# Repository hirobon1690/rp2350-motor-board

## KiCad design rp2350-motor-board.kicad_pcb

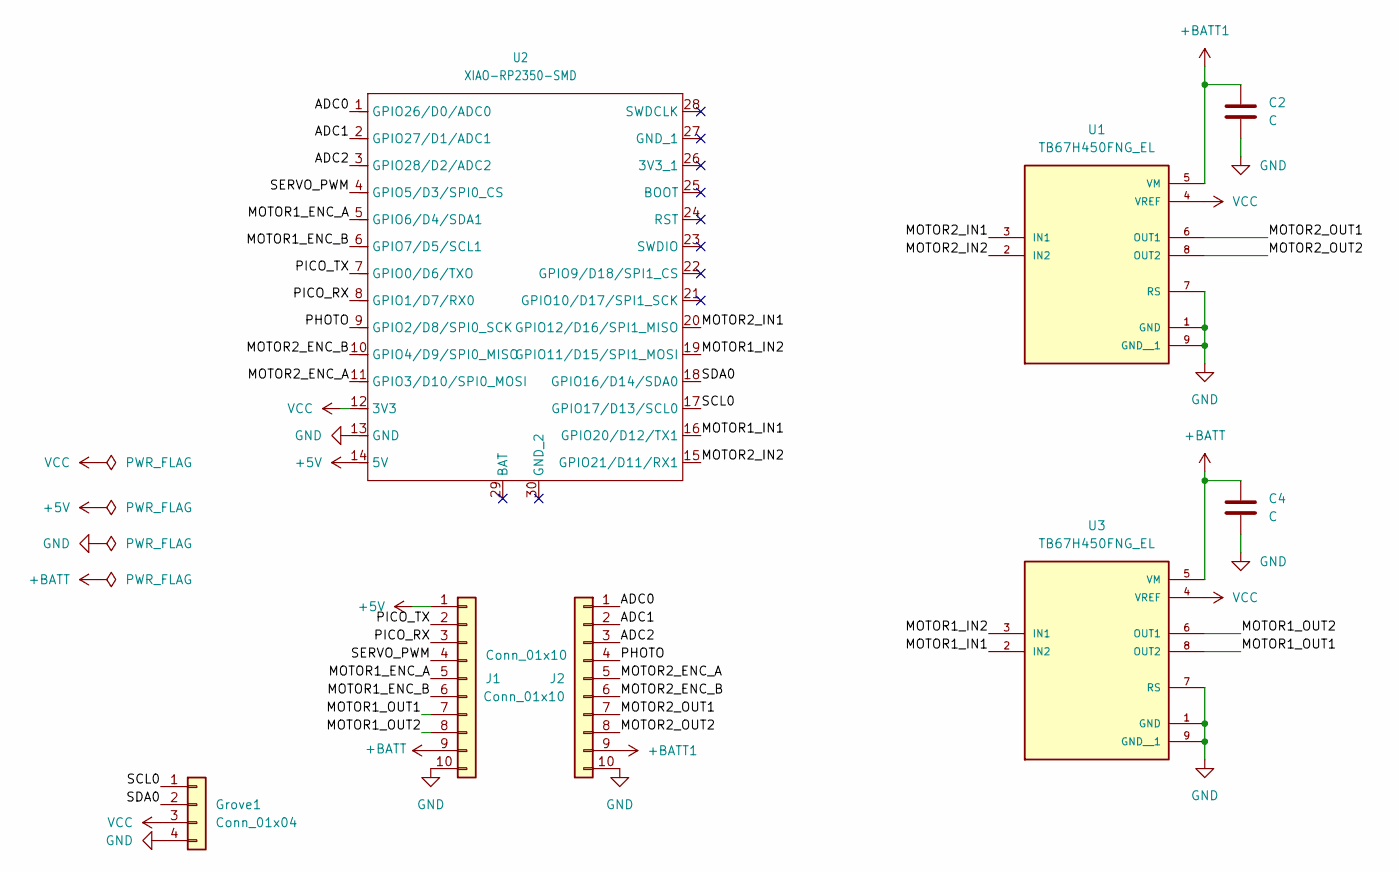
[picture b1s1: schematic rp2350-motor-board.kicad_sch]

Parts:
C2, C4: C; C_0805_2012Metric_Pad1.18x1.45mm_HandSolder
Grove1: Conn_01x04; JST_PH_S4B-PH-K_1x04_P2.00mm_Horizontal
J1, J2: Conn_01x10; PinSocket_1x10_P2.54mm_Vertical
U1, U3: TB67H450FNG_EL; SOIC127P599X175-9N; PARTREV 3.0
U2: XIAO-RP2350-SMD

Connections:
+5V: J1.1, U2.14 (5V)
+BATT: C4.1, J1.9, U3.5 (VM)
+BATT1: C2.1, J2.9, U1.5 (VM)
/ADC0: J2.1, U2.1 (GPIO26/D0/ADC0)
/ADC1: J2.2, U2.2 (GPIO27/D1/ADC1)
/ADC2: J2.3, U2.3 (GPIO28/D2/ADC2)
/MOTOR1_ENC_A: J1.5, U2.5 (GPIO6/D4/SDA1)
/MOTOR1_ENC_B: J1.6, U2.6 (GPIO7/D5/SCL1)
/MOTOR1_IN1: U2.16 (GPIO20/D12/TX1), U3.2 (IN2)
/MOTOR1_IN2: U2.19 (GPIO11/D15/SPI1_MOSI), U3.3 (IN1)
/MOTOR1_OUT1: J1.7, U3.8 (OUT2)
/MOTOR1_OUT2: J1.8, U3.6 (OUT1)
/MOTOR2_ENC_A: J2.5, U2.11 (GPIO3/D10/SPI0_MOSI)
/MOTOR2_ENC_B: J2.6, U2.10 (GPIO4/D9/SPI0_MISO)
/MOTOR2_IN1: U1.3 (IN1), U2.20 (GPIO12/D16/SPI1_MISO)
/MOTOR2_IN2: U1.2 (IN2), U2.15 (GPIO21/D11/RX1)
/MOTOR2_OUT1: J2.7, U1.6 (OUT1)
/MOTOR2_OUT2: J2.8, U1.8 (OUT2)
/PHOTO: J2.4, U2.9 (GPIO2/D8/SPI0_SCK)
/PICO_RX: J1.3, U2.8 (GPIO1/D7/RX0)
/PICO_TX: J1.2, U2.7 (GPIO0/D6/TXO)
/SCL0: Grove1.1, U2.17 (GPIO17/D13/SCL0)
/SDA0: Grove1.2, U2.18 (GPIO16/D14/SDA0)
/SERVO_PWM: J1.4, U2.4 (GPIO5/D3/SPI0_CS)
GND: C2.2, C4.2, Grove1.4, J1.10, J2.10, U1.1 (GND), U1.7 (RS), U1.9 (GND__1), U2.13 (GND), U3.1 (GND), U3.7 (RS), U3.9 (GND__1)
VCC: Grove1.3, U1.4 (VREF), U2.12 (3V3), U3.4 (VREF)

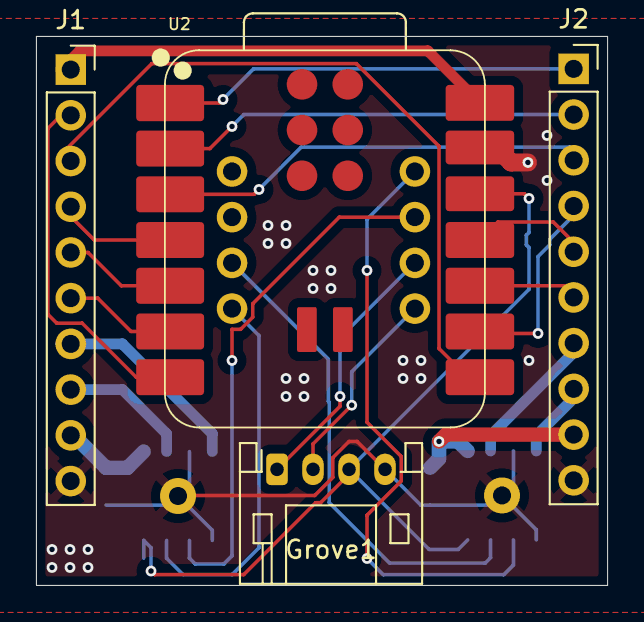
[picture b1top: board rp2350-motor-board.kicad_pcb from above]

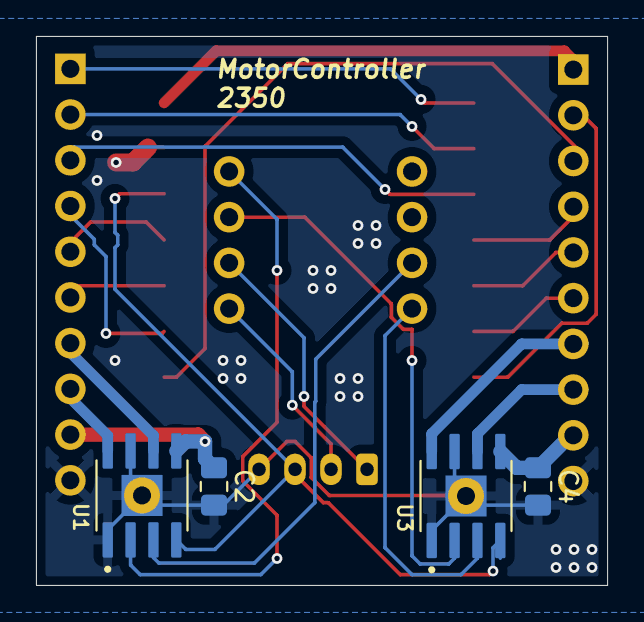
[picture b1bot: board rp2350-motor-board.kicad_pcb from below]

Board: 2 copper layers, 31.7 x 30.5 mm, 8 parts (4 on the bottom side), 26 nets.

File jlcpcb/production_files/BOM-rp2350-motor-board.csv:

Comment,Designator,Footprint,LCSC,Quantity
Conn_01x10,J2,PinSocket_1x10_P2.54mm_Vertical,,1
Conn_01x04,Grove1,JST_PH_S4B-PH-K_1x04_P2.00mm_Horizontal,,1
Conn_01x10,J1,PinSocket_1x10_P2.54mm_Vertical,,1
XIAO-RP2350-SMD,U2,XIAO-RP2350-SMD,,1
C,C4,C_0805_2012Metric_Pad1.18x1.45mm_HandSolder,,1
C,C2,C_0805_2012Metric_Pad1.18x1.45mm_HandSolder,,1
TB67H450FNG_EL,U1,SOIC127P599X175-9N,,1
TB67H450FNG_EL,U3,SOIC127P599X175-9N,,1
